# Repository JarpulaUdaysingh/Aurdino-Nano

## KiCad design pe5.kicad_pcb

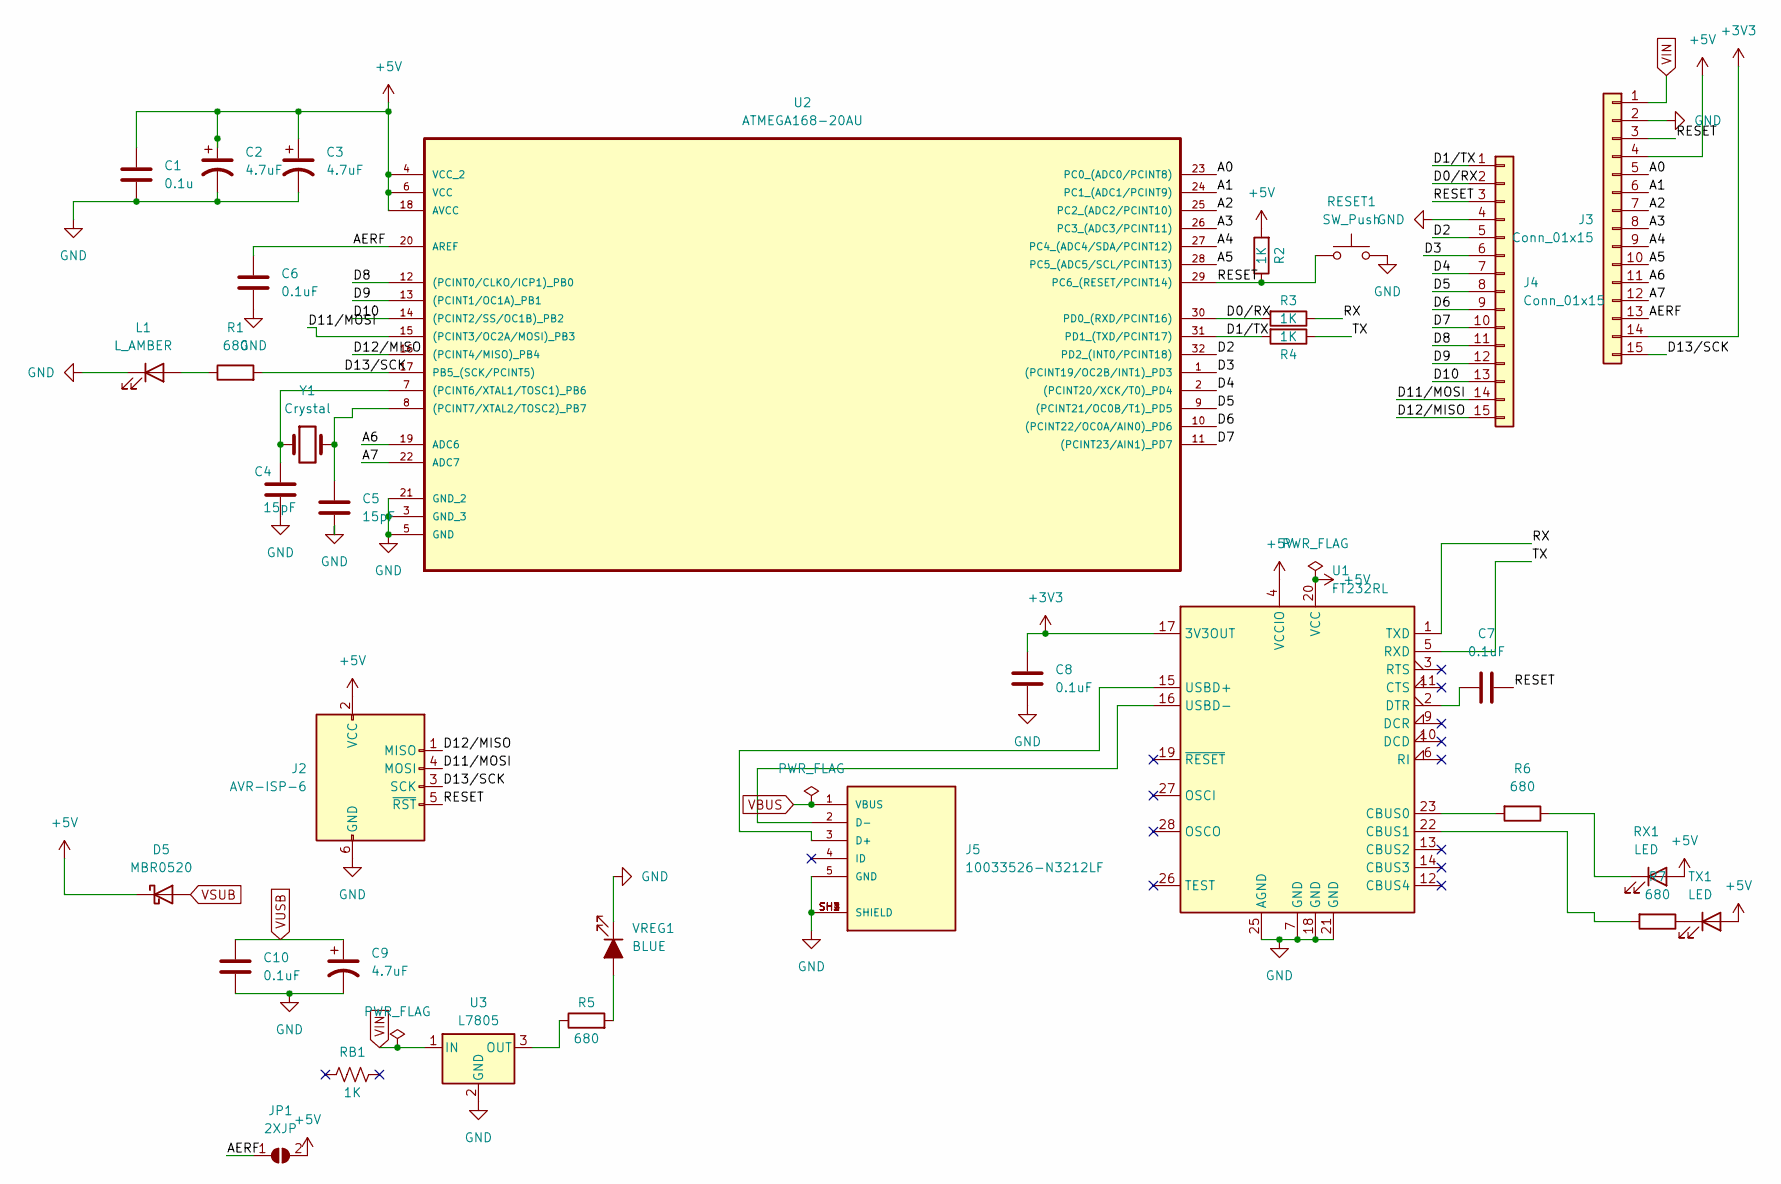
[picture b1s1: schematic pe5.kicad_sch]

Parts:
C1: 0.1u; C_0805_2012Metric
C2, C3, C9: 4.7uF; C_0805_2012Metric
C4, C5: 15pF; C_0805_2012Metric
C6, C7, C8, C10: 0.1uF; C_0805_2012Metric
D5: MBR0520; D_SOD-123
J2: AVR-ISP-6; IDC-Header_2x03_P2.54mm_Vertical
J3, J4: Conn_01x15; PinHeader_1x15_P2.54mm_Vertical
J5: 10033526-N3212LF; AMPHENOL_10033526-N3212LF
JP1: 2XJP; SolderJumper-2_P1.3mm_Open_Pad1.0x1.5mm
L1: L_AMBER; LED_0805_2012Metric
R1, R5, R6, R7: 680; R_0805_2012Metric
R2, R3, R4: 1K; R_0805_2012Metric
RB1: 1K; R_0805_2012Metric
RESET1: SW_Push; SW_SPST_B3U-1000P
RX1: LED; LED_Kingbright_APHBM2012_2x1.25mm
TX1: LED; LED_Kingbright_APHBM2012_2x1.25mm
U1: FT232RL; SSOP-28_5.3x10.2mm_P0.65mm
U2: ATMEGA168-20AU; QFP80P900X900X120-32N; MPN ATMEGA168-20AU
U3: L7805; SOT-223-3_TabPin2
VREG1: BLUE; LED_0805_2012Metric
Y1: Crystal; Crystal_HC49-4H_Vertical

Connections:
+3V3: C8.1, J3.14, U1.17 (3V3OUT)
+5V: C1.1, C2.1, C3.1, D5.1 (K), J2.2 (VCC), J3.4, JP1.2 (B), R2.2, RX1.2 (A), TX1.2 (A), U1.4 (VCCIO), U1.20 (VCC), U2.4 (VCC_2), U2.6 (VCC), U2.18 (AVCC)
/A0: J3.5, U2.23 (PC0_(ADC0/PCINT8))
/A1: J3.6, U2.24 (PC1_(ADC1/PCINT9))
/A2: J3.7, U2.25 (PC2_(ADC2/PCINT10))
/A3: J3.8, U2.26 (PC3_(ADC3/PCINT11))
/A4: J3.9, U2.27 (PC4_(ADC4/SDA/PCINT12))
/A5: J3.10, U2.28 (PC5_(ADC5/SCL/PCINT13))
/A6: J3.11, U2.19 (ADC6)
/A7: J3.12, U2.22 (ADC7)
/AERF: C6.1, J3.13, JP1.1 (A), U2.20 (AREF)
/D0/RX: J4.2, R3.2, U2.30 (PD0_(RXD/PCINT16))
/D1/TX: J4.1, R4.2, U2.31 (PD1_(TXD/PCINT17))
/D2: J4.5, U2.32 (PD2_(INT0/PCINT18))
/D3: J4.6, U2.1 ((PCINT19/OC2B/INT1)_PD3)
/D4: J4.7, U2.2 ((PCINT20/XCK/T0)_PD4)
/D5: J4.8, U2.9 ((PCINT21/OC0B/T1)_PD5)
/D6: J4.9, U2.10 ((PCINT22/OC0A/AIN0)_PD6)
/D7: J4.10, U2.11 ((PCINT23/AIN1)_PD7)
/D8: J4.11, U2.12 ((PCINT0/CLKO/ICP1)_PB0)
/D9: J4.12, U2.13 ((PCINT1/OC1A)_PB1)
/D10: J4.13, U2.14 ((PCINT2/SS/OC1B)_PB2)
/D11/MOSI: J2.4 (MOSI), J4.14, U2.15 ((PCINT3/OC2A/MOSI)_PB3)
/D12/MISO: J2.1 (MISO), J4.15, U2.16 ((PCINT4/MISO)_PB4)
/D13/SCK: J2.3 (SCK), J3.15, R1.2, U2.17 (PB5_(SCK/PCINT5))
/RESET: C7.1, J2.5 (~RST), J3.3, J4.3, R2.1, RESET1.1, U2.29 (PC6_(RESET/PCINT14))
/RX: R3.1, U1.1 (TXD)
/TX: R4.1, U1.5 (RXD)
GND: C1.2, C2.2, C3.2, C4.2, C5.2, C6.2, C8.2, C9.2, C10.2, J2.6 (GND), J3.2, J4.4, J5.5 (GND), J5.SH1 (SHIELD), J5.SH2 (SHIELD), J5.SH3 (SHIELD), J5.SH4 (SHIELD), L1.1 (K), RESET1.2, U1.7 (GND), U1.18 (GND), U1.21 (GND), U1.25 (AGND), U2.3 (GND_3), U2.5 (GND), U2.21 (GND_2), U3.2 (GND), VREG1.1 (K)
unnamed: J5.3 (D+), U1.15 (USBD+)
unnamed: J5.2 (D-), U1.16 (USBD-)
unnamed: L1.2 (A), R1.1
unnamed: R6.1, RX1.1 (K)
unnamed: R7.1, TX1.1 (K)
unnamed: R6.2, U1.23 (CBUS0)
unnamed: R7.2, U1.22 (CBUS1)
unnamed: C7.2, U1.2 (DTR)
unnamed: C4.1, U2.7 ((PCINT6/XTAL1/TOSC1)_PB6), Y1.1
unnamed: C5.1, U2.8 ((PCINT7/XTAL2/TOSC2)_PB7), Y1.2
unnamed: R5.1, U3.3 (OUT)
unnamed: R5.2, VREG1.2 (A)
VIN: J3.1, U3.1 (IN)
VSUB: D5.2 (A)
VUSB: C9.1, C10.1

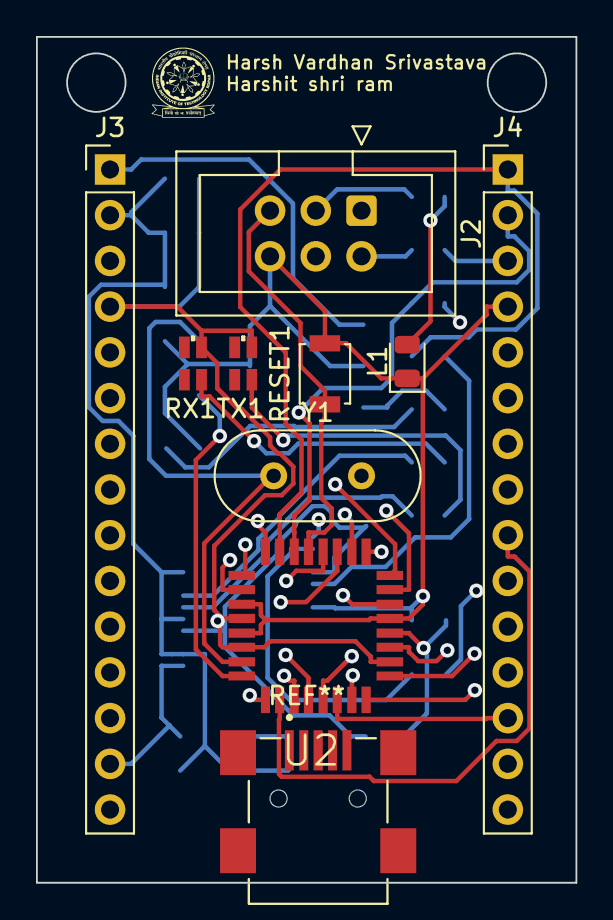
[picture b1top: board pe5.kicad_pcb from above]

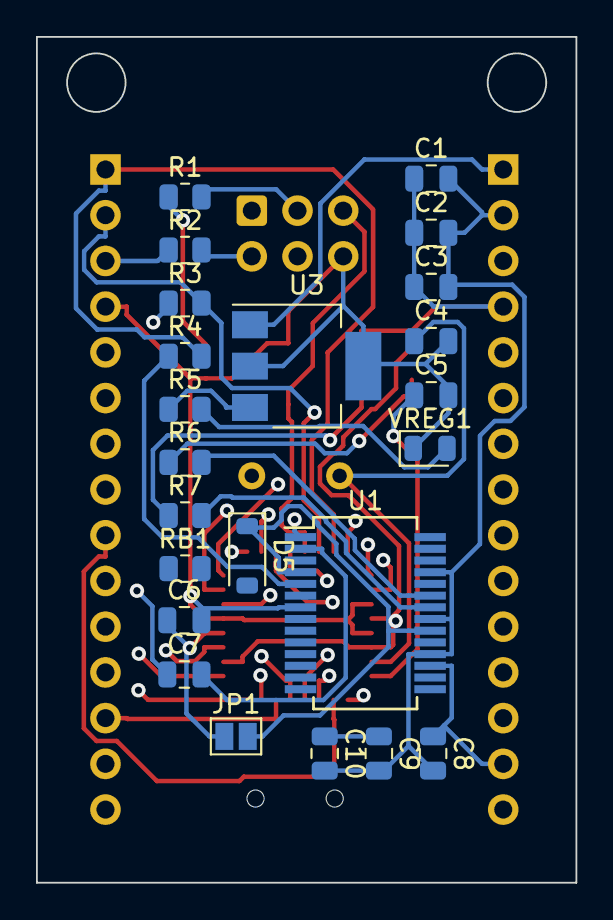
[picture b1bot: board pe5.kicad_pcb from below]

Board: 4 copper layers, 30.0 x 47.0 mm, 32 parts (23 on the bottom side), 41 nets.
